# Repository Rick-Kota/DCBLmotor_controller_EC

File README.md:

# DCBLmotor_controller_EC
Electric Circuit data for DCBLmotor controller (in develop)

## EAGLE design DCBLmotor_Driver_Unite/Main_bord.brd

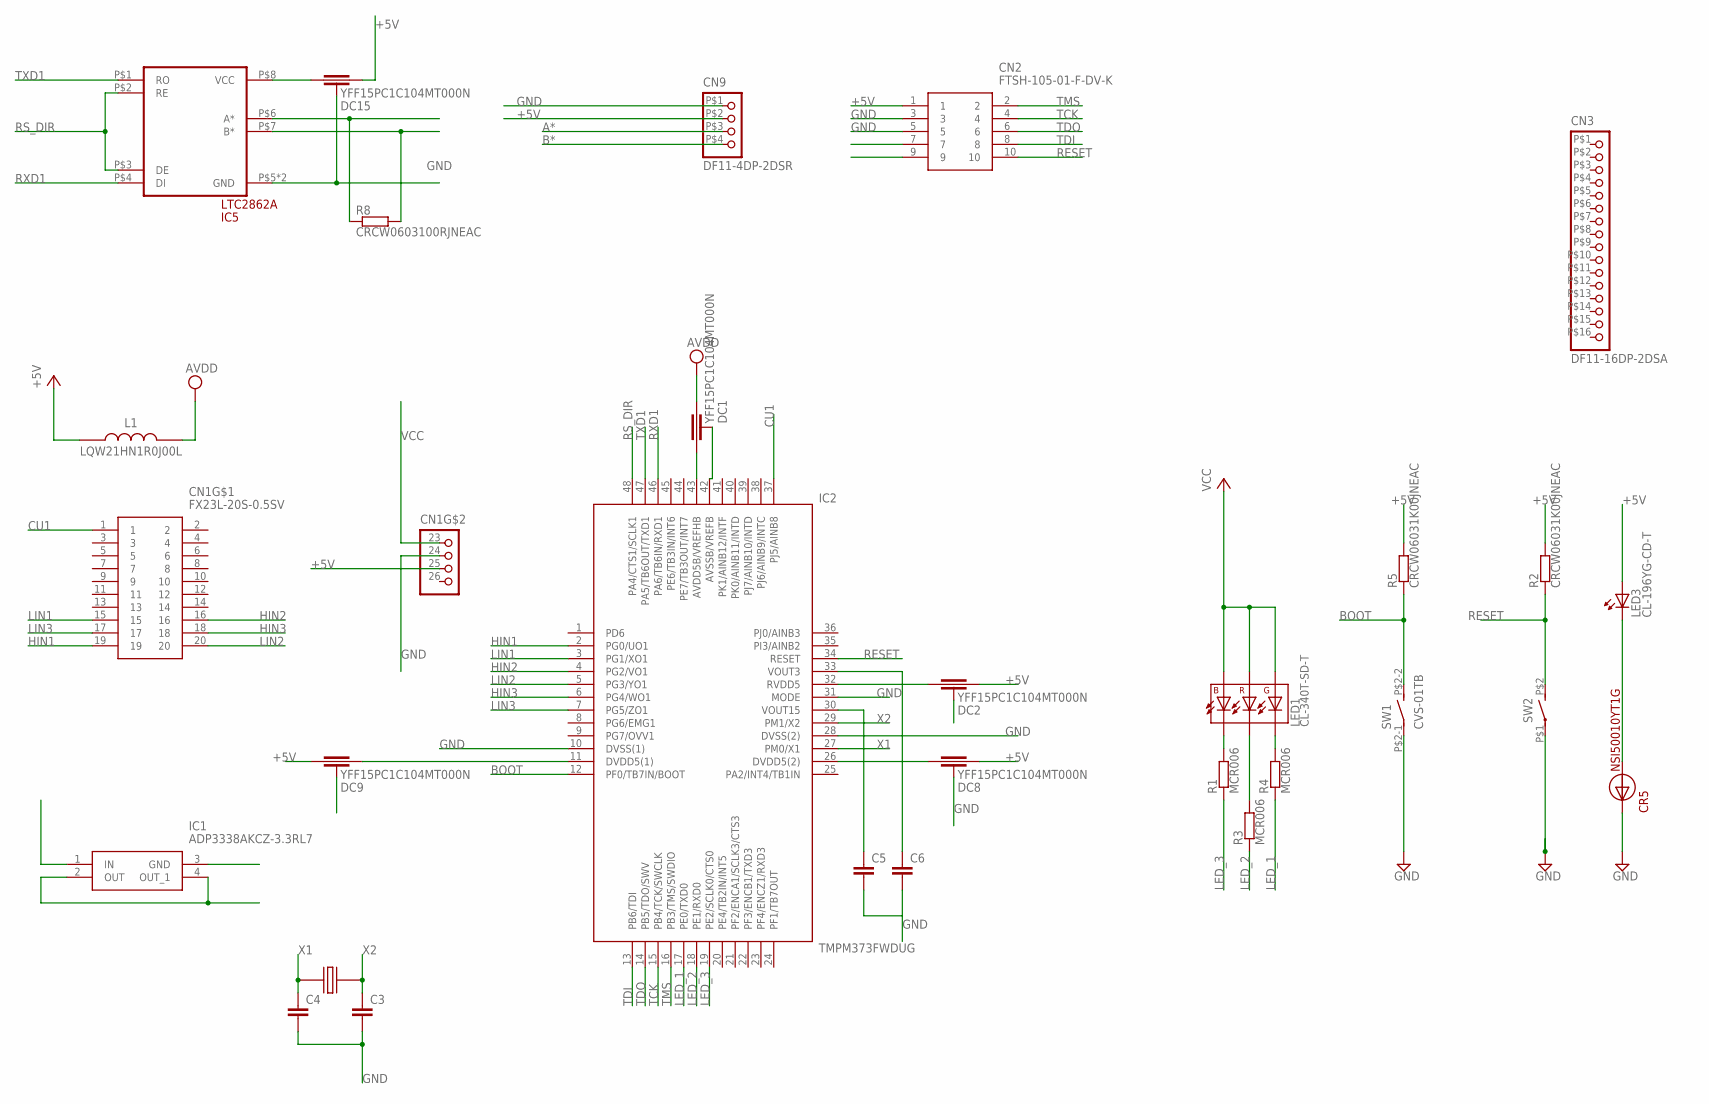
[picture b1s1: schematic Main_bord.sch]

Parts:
C3, C4: GRM0225C1E120JA03L; 0402
C5, C6: GRM035R60J475ME15D; 0603
CN1: FX23L-20S-0.5SV
CN2: FTSH-105-01-F-DV-K; SAMTEC_FTSH-105-01-L-DV
CN3: DF11-16DP-2DSA; DF11-16DP-2D
CN9: DF11-4DP-2DSR; DF11_4DP-2D
CR5: NSI50010YT1G; SOD-123
DC1, DC2, DC8, DC9, DC15: YFF15PC1C104MT000N; YFF15PC
IC1: ADP3338AKCZ-3.3RL7; SOT230P700X180-4N
IC2: TMPM373FWDUG; QFP50P900X900X160-48N
IC5: LTC2862A; DD_PACKGE_8
L1: LQW21HN1R0J00L; INDC2012X100N
LED1: CL-340T-SD-T; CL-340
LED3: CL-196YG-CD-T; CL-196
R1, R3, R4: MCR006
R2, R5: CRCW06031K00JNEAC; 0603
R8: CRCW0603100RJNEAC; 0603
SW1: CVS-01TB; CVS-01B
SW2: EVQ-PE104K; EVQ
XTAL1: ABM8AIG-10.000MHZ-12-2Z-T3; ABM8AIG

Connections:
+3.3V: IC1.2 (OUT), IC1.4 (OUT_1)
+5V: CN1.25 (3), CN2.1, CN9.P$2 (2), DC2.P$2, DC8.P$2, DC9.P$1, DC15.P$2, IC1.1 (IN), L1.1, LED1.P$1 (A_G), LED1.P$2 (R_A), LED1.P$3 (B_A), LED3.P$A (A), R2.P$1 (1), R5.P$1 (1)
A*: CN9.P$3 (3), IC5.P$6 (A*), R8.P$2 (2)
AVDD: DC1.P$2, L1.2
B*: CN9.P$4 (4), IC5.P$7 (B*), R8.P$1 (1)
BOOT: IC2.12 (PF0/TB7IN/BOOT), R5.P$2 (2), SW1.P$2-2 (S)
CU1: CN1.1, IC2.37 (PJ5/AINB8)
GND: C3.P$2 (2), C4.P$2 (2), C5.P$2 (2), C6.P$2 (2), CN1.24 (2), CN2.3, CN2.5, CN9.P$1 (1), CR5.P$C, DC1.P$3 (GND), DC1.P$4 (GND), DC2.P$3 (GND), DC2.P$4 (GND), DC8.P$3 (GND), DC8.P$4 (GND), DC9.P$3 (GND), DC9.P$4 (GND), DC15.P$3 (GND), DC15.P$4 (GND), IC1.3 (GND), IC2.10 (DVSS(1)), IC2.28 (DVSS(2)), IC2.31 (MODE), IC2.42 (AVSSB/VREFB), IC5.P$5 (GND), IC5.PAD (GND), SW1.P$2-1, SW2.P$1
HIN1: CN1.19, IC2.2 (PG0/UO1)
HIN2: CN1.16, IC2.4 (PG2/VO1)
HIN3: CN1.18, IC2.6 (PG4/WO1)
LED_1: IC2.17 (PE0/TXD0), R4.P$2 (2)
LED_2: IC2.18 (PE1/RXD0), R3.P$2 (2)
LED_3: IC2.19 (PE2/SCLK0/CTS0), R1.P$2 (2)
LIN1: CN1.15, IC2.3 (PG1/XO1)
LIN2: CN1.20, IC2.5 (PG3/YO1)
LIN3: CN1.17, IC2.7 (PG5/ZO1)
unnamed: DC2.P$1, IC2.32 (RVDD5)
unnamed: DC1.P$1, IC2.43 (AVDD5B/VREFHB)
unnamed: LED1.P$5 (R_C), R3.P$1 (1)
unnamed: LED1.P$4 (B_C), R1.P$1 (1)
unnamed: LED1.P$6 (G_C), R4.P$1 (1)
unnamed: C5.P$1 (1), IC2.30 (VOUT15)
unnamed: C6.P$1 (1), IC2.33 (VOUT3)
unnamed: DC8.P$1, IC2.26 (DVDD5(2))
unnamed: DC9.P$2, IC2.11 (DVDD5(1))
unnamed: CR5.P$A, LED3.P$C (C)
unnamed: DC15.P$1, IC5.P$8 (VCC)
RESET: CN2.10, IC2.34 (RESET), R2.P$2 (2), SW2.P$2 (S)
RS_DIR: IC2.48 (PA4/CTS1/SCLK1), IC5.P$2 (RE), IC5.P$3 (DE)
RXD1: IC2.46 (PA6/TB6IN/RXD1), IC5.P$4 (DI)
TCK: CN2.4, IC2.15 (PB4/TCK/SWCLK)
TDI: CN2.8, IC2.13 (PB6/TDI)
TDO: CN2.6, IC2.14 (PB5/TDO/SWV)
TMS: CN2.2, IC2.16 (PB3/TMS/SWDIO)
TXD1: IC2.47 (PA5/TB6OUT/TXD1), IC5.P$1 (RO)
VCC: CN1.23 (1)
X1: C4.P$1 (1), IC2.27 (PM0/X1), XTAL1.P$1
X2: C3.P$1 (1), IC2.29 (PM1/X2), XTAL1.P$3

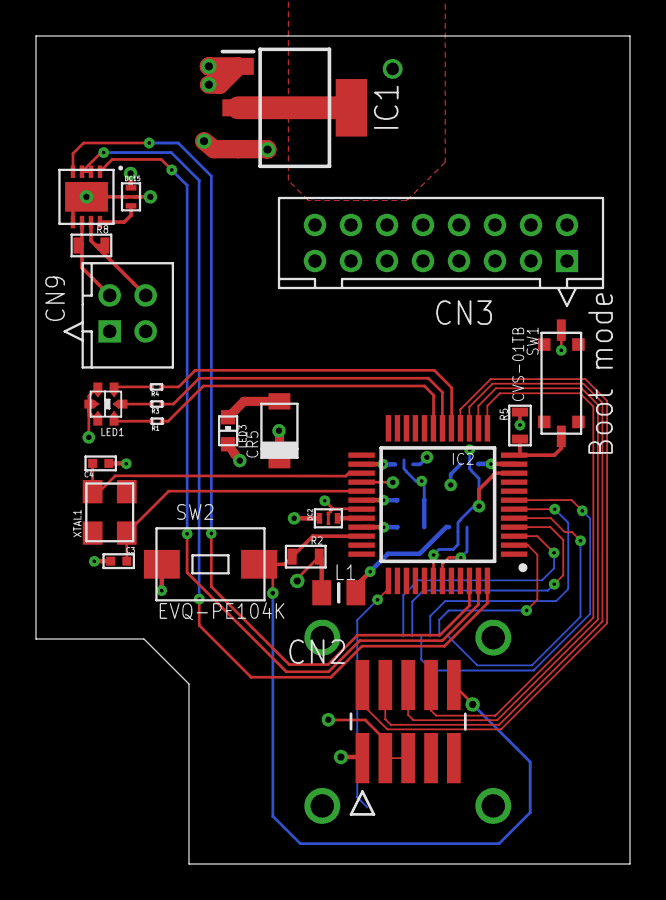
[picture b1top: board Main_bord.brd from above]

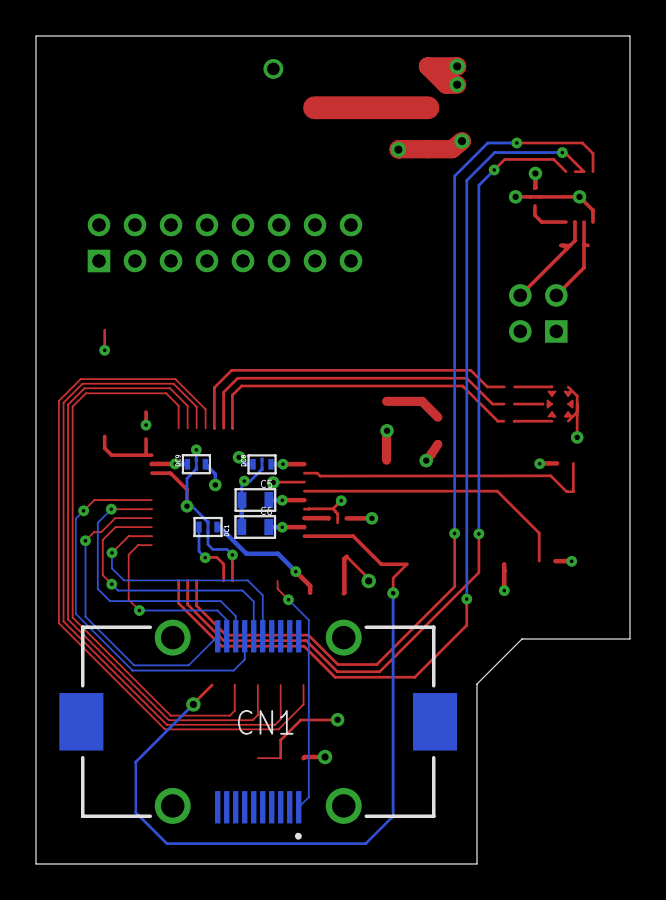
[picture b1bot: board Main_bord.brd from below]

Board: 4 copper layers, 33.0 x 46.0 mm, 29 parts (6 on the bottom side), 38 nets.

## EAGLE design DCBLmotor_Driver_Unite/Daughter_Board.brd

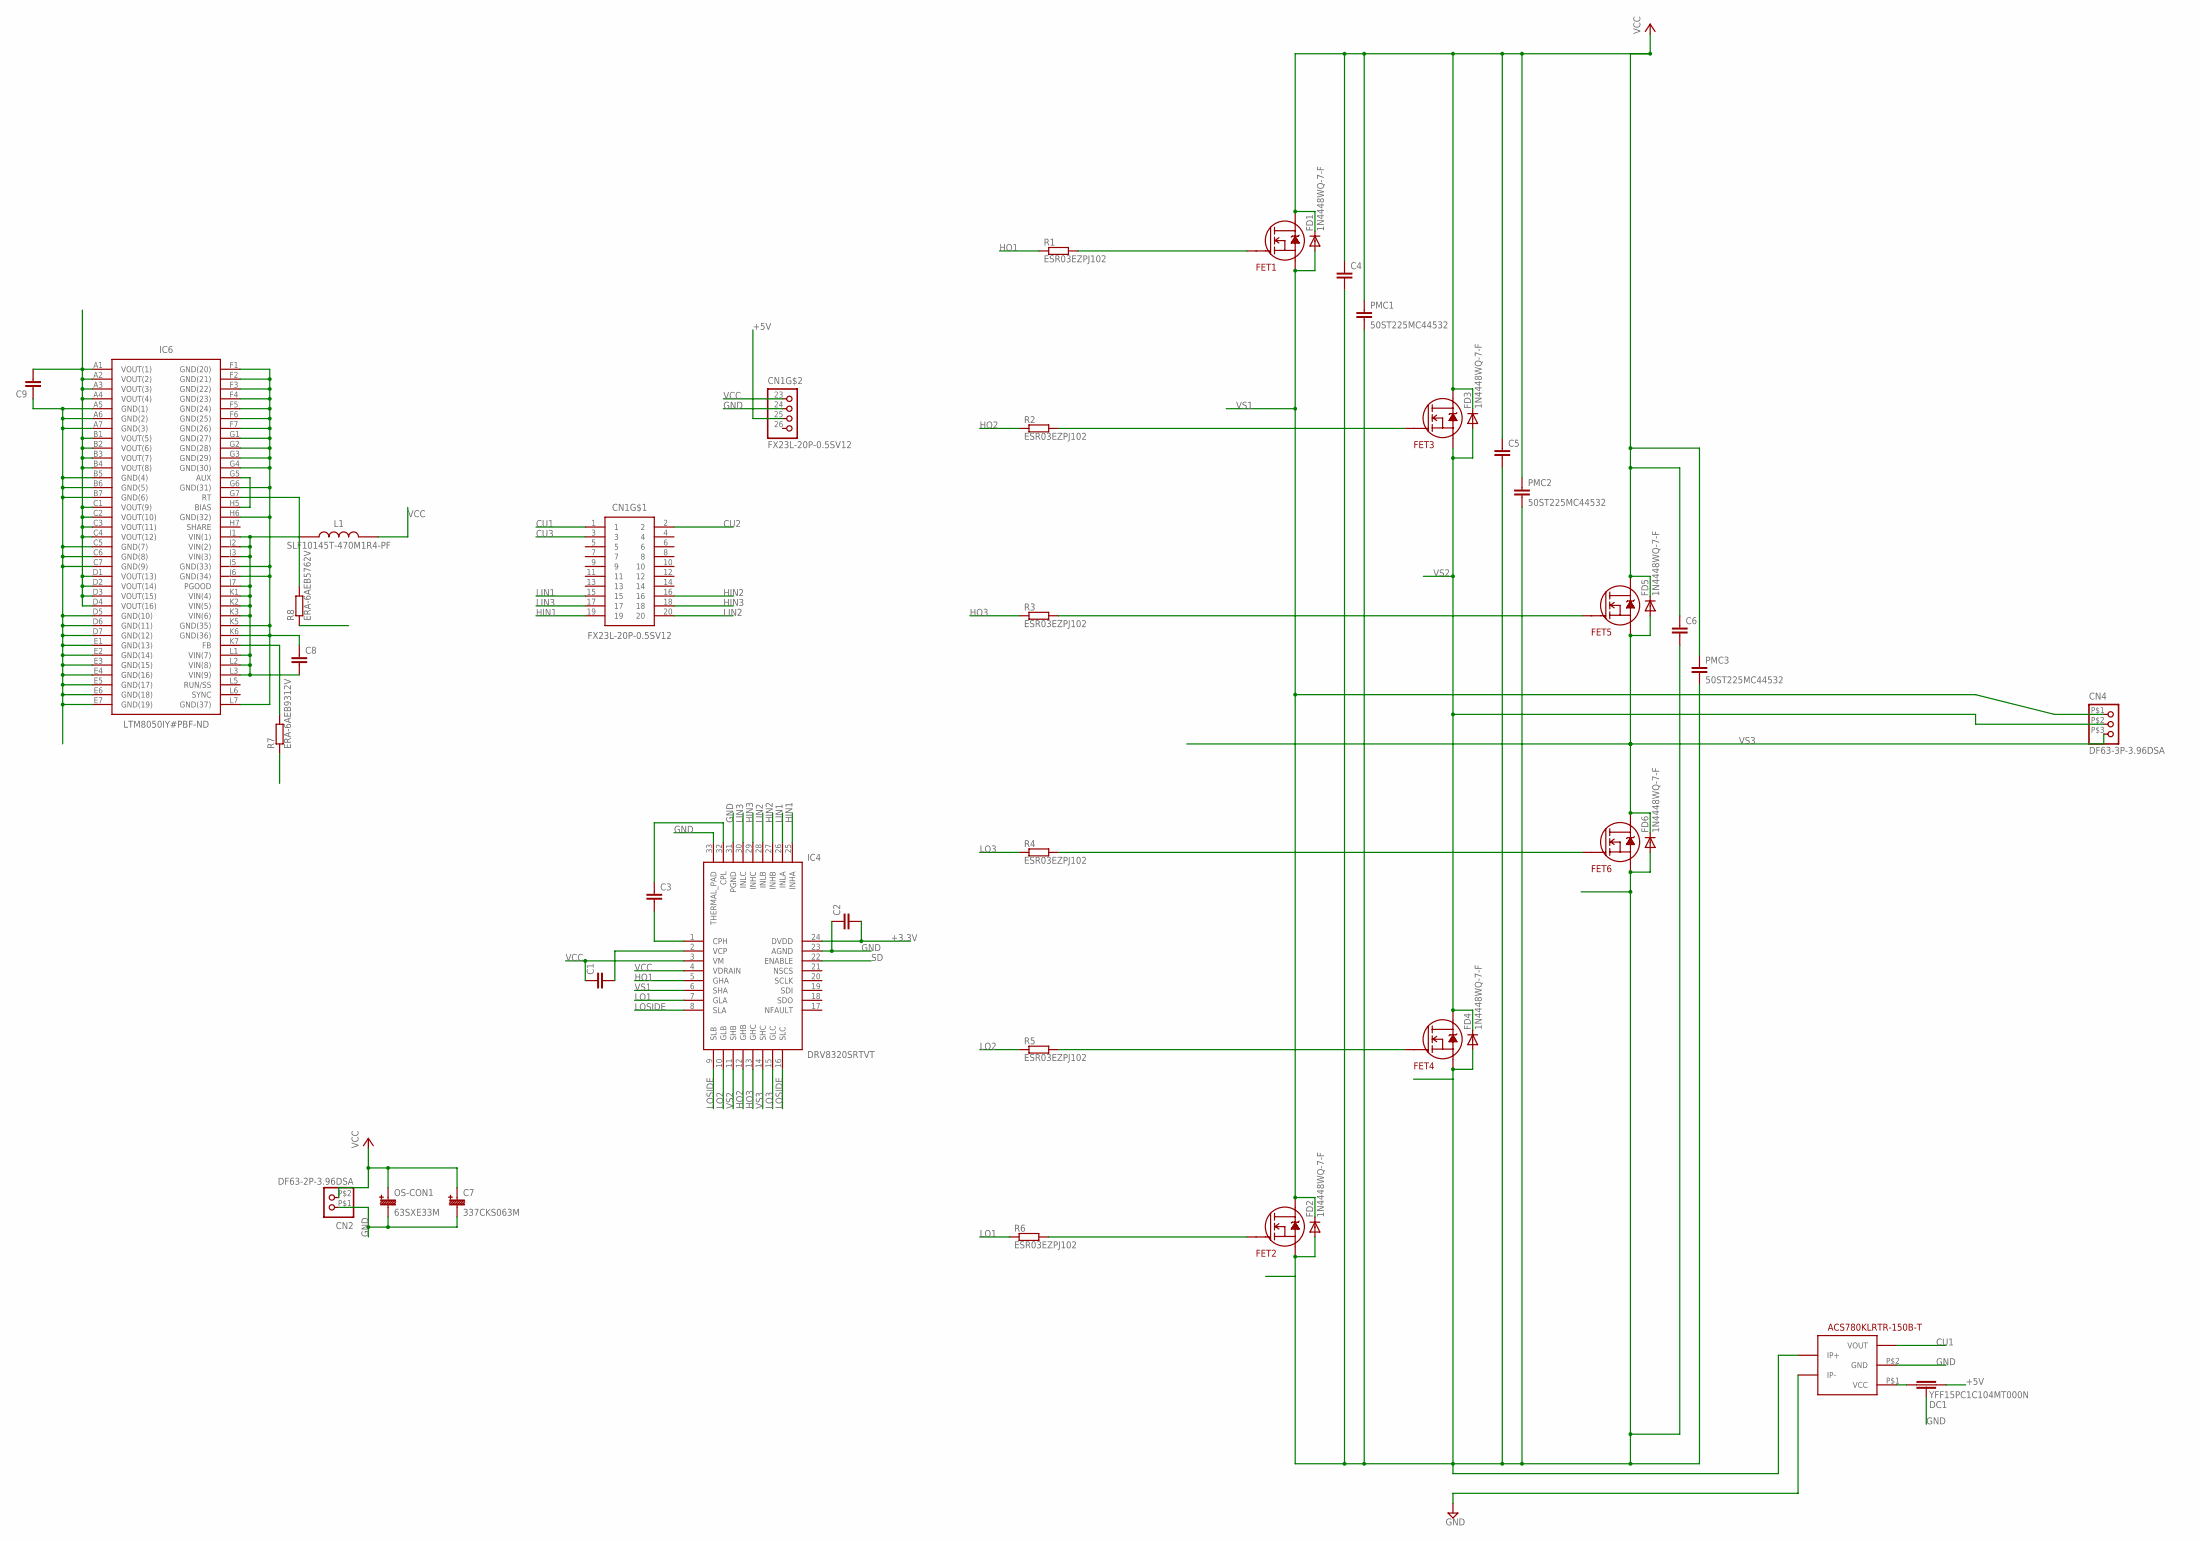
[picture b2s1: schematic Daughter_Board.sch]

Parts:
C1, C2, C4, C5, C6: CKG32KX7R1H105M335AJ; CGK32K
C3: CGA2B3X7R1H473K050BB; C0402
C7: 337CKS063M; 10
C8: CGA6M3X7S2A475M200AB; C1210
C9: GRM035R60J475ME15D; 0603
CN1: FX23L-20P-0.5SV12
CN2: DF63-2P-3.96DSA
CN4: DF63-3P-3.96DSA
DC1: YFF15PC1C104MT000N; YFF15PC
FD1, FD2, FD3, FD4, FD5, FD6: 1N4448WQ-7-F; SOD123
FET1, FET2, FET3, FET4, FET5, FET6: IRF7480MTRPBF; DIRECT_FET_ME
IC1: ACS780KLRTR-150B-T; 7-PIN_PSOP
IC4: DRV8320SRTVT; QFN50P500X500X80-33N
IC6: LTM8050IY#PBF-ND; BGA70C127P7X11_900X1500X512
L1: SLF10145T-470M1R4-PF; SLF10145
OS-CON1: 63SXE33M; E12
PMC1, PMC2, PMC3: 50ST225MC44532; 4532
R1, R2, R3, R4, R5, R6: ESR03EZPJ102; ESR03
R7: ERA-6AEB9312V; R0805
R8: ERA-6AEB5762V; R0805

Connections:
+3.3V: C2.P$2 (2), IC4.24 (DVDD)
+5V: C9.P$2 (2), CN1.25 (3), DC1.P$2, IC6.A1 (VOUT(1)), IC6.A2 (VOUT(2)), IC6.A3 (VOUT(3)), IC6.A4 (VOUT(4)), IC6.B1 (VOUT(5)), IC6.B2 (VOUT(6)), IC6.B3 (VOUT(7)), IC6.B4 (VOUT(8)), IC6.C1 (VOUT(9)), IC6.C2 (VOUT(10)), IC6.C3 (VOUT(11)), IC6.C4 (VOUT(12)), IC6.D1 (VOUT(13)), IC6.D2 (VOUT(14)), IC6.D3 (VOUT(15)), IC6.D4 (VOUT(16))
CU1: CN1.1, IC1.P$3 (VOUT)
CU2: CN1.2
CU3: CN1.3
GND: C2.P$1 (1), C7.P$- (2), C8.P$1 (1), C9.P$1 (1), CN1.24 (2), CN2.P$1 (1), DC1.P$3 (GND), DC1.P$4 (GND), IC1.P$2 (GND), IC1.P$6 (IP-), IC4.23 (AGND), IC4.31 (PGND), IC4.33 (THERMAL_PAD), IC6.A5 (GND(1)), IC6.A6 (GND(2)), IC6.A7 (GND(3)), IC6.B5 (GND(4)), IC6.B6 (GND(5)), IC6.B7 (GND(6)), IC6.C5 (GND(7)), IC6.C6 (GND(8)), IC6.C7 (GND(9)), IC6.D5 (GND(10)), IC6.D6 (GND(11)), IC6.D7 (GND(12)), IC6.E1 (GND(13)), IC6.E2 (GND(14)), IC6.E3 (GND(15)), IC6.E4 (GND(16)), IC6.E5 (GND(17)), IC6.E6 (GND(18)), IC6.E7 (GND(19)), IC6.F1 (GND(20)), IC6.F2 (GND(21)), IC6.F3 (GND(22)), IC6.F4 (GND(23)), IC6.F5 (GND(24)), IC6.F6 (GND(25)), IC6.F7 (GND(26)), IC6.G1 (GND(27)), IC6.G2 (GND(28)), IC6.G3 (GND(29)), IC6.G4 (GND(30)), IC6.G6 (GND(31)), IC6.H6 (GND(32)), IC6.J5 (GND(33)), IC6.J6 (GND(34)), IC6.K5 (GND(35)), IC6.K6 (GND(36)), IC6.L7 (GND(37)), OS-CON1.P$- (2), R7.2, R8.2
HIN1: CN1.19, IC4.25 (INHA)
HIN2: CN1.16, IC4.27 (INHB)
HIN3: CN1.18, IC4.29 (INHC)
HO1: IC4.5 (GHA), R1.P$2 (2)
HO2: IC4.12 (GHB), R2.P$2 (2)
HO3: IC4.13 (GHC), R3.P$2 (2)
IN_A: C8.P$2 (2), IC6.J1 (VIN(1)), IC6.J2 (VIN(2)), IC6.J3 (VIN(3)), IC6.J7 (PGOOD), IC6.K1 (VIN(4)), IC6.K2 (VIN(5)), IC6.K3 (VIN(6)), IC6.L1 (VIN(7)), IC6.L2 (VIN(8)), IC6.L3 (VIN(9)), L1.P$1 (1)
LIN1: CN1.15, IC4.26 (INLA)
LIN2: CN1.20, IC4.28 (INLB)
LIN3: CN1.17, IC4.30 (INLC)
LO1: IC4.7 (GLA), R6.P$2 (2)
LO2: IC4.10 (GLB), R5.P$2 (2)
LO3: IC4.15 (GLC), R4.P$2 (2)
LOSIDE: C4.P$2 (2), C5.P$2 (2), C6.P$2 (2), FD2.A, FD4.A, FD6.A, FET2.S1 (S), FET2.S2 (S), FET2.S3 (S), FET2.S4 (S), FET4.S1 (S), FET4.S2 (S), FET4.S3 (S), FET4.S4 (S), FET6.S1 (S), FET6.S2 (S), FET6.S3 (S), FET6.S4 (S), IC1.P$5 (IP+), IC4.8 (SLA), IC4.9 (SLB), IC4.16 (SLC), PMC1.P$2 (2), PMC2.P$2 (2), PMC3.P$2 (2)
unnamed: IC6.G5 (AUX), IC6.H5 (BIAS)
unnamed: FET4.G1 (G), FET4.G2 (G), R5.P$1 (1)
unnamed: IC6.K7 (FB), R7.1
unnamed: FET2.G1 (G), FET2.G2 (G), R6.P$1 (1)
unnamed: C1.P$2 (2), IC4.2 (VCP)
unnamed: IC6.G7 (RT), R8.1
unnamed: C3.P$2 (2), IC4.1 (CPH)
unnamed: C3.P$1 (1), IC4.32 (CPL)
unnamed: DC1.P$1, IC1.P$1 (VCC)
unnamed: FET6.G1 (G), FET6.G2 (G), R4.P$1 (1)
unnamed: FET5.G1 (G), FET5.G2 (G), R3.P$1 (1)
unnamed: FET3.G1 (G), FET3.G2 (G), R2.P$1 (1)
unnamed: FET1.G1 (G), FET1.G2 (G), R1.P$1 (1)
SD: IC4.22 (ENABLE)
VCC: C1.P$1 (1), C4.P$1 (1), C5.P$1 (1), C6.P$1 (1), C7.P$+ (+), CN1.23 (1), CN2.P$2 (2), FD1.K (C), FD3.K (C), FD5.K (C), FET1.P$1 (D), FET1.P$2 (D), FET1.P$3 (D), FET1.P$4 (D), FET3.P$1 (D), FET3.P$2 (D), FET3.P$3 (D), FET3.P$4 (D), FET5.P$1 (D), FET5.P$2 (D), FET5.P$3 (D), FET5.P$4 (D), IC4.3 (VM), IC4.4 (VDRAIN), L1.P$2 (2), OS-CON1.P$+ (+), PMC1.P$1 (1), PMC2.P$1 (1), PMC3.P$1 (1)
VS1: CN4.P$1 (1), FD1.A, FD2.K (C), FET1.S1 (S), FET1.S2 (S), FET1.S3 (S), FET1.S4 (S), FET2.P$1 (D), FET2.P$2 (D), FET2.P$3 (D), FET2.P$4 (D), IC4.6 (SHA)
VS2: CN4.P$2 (2), FD3.A, FD4.K (C), FET3.S1 (S), FET3.S2 (S), FET3.S3 (S), FET3.S4 (S), FET4.P$1 (D), FET4.P$2 (D), FET4.P$3 (D), FET4.P$4 (D), IC4.11 (SHB)
VS3: CN4.P$3 (3), FD5.A, FD6.K (C), FET5.S1 (S), FET5.S2 (S), FET5.S3 (S), FET5.S4 (S), FET6.P$1 (D), FET6.P$2 (D), FET6.P$3 (D), FET6.P$4 (D), IC4.14 (SHC)

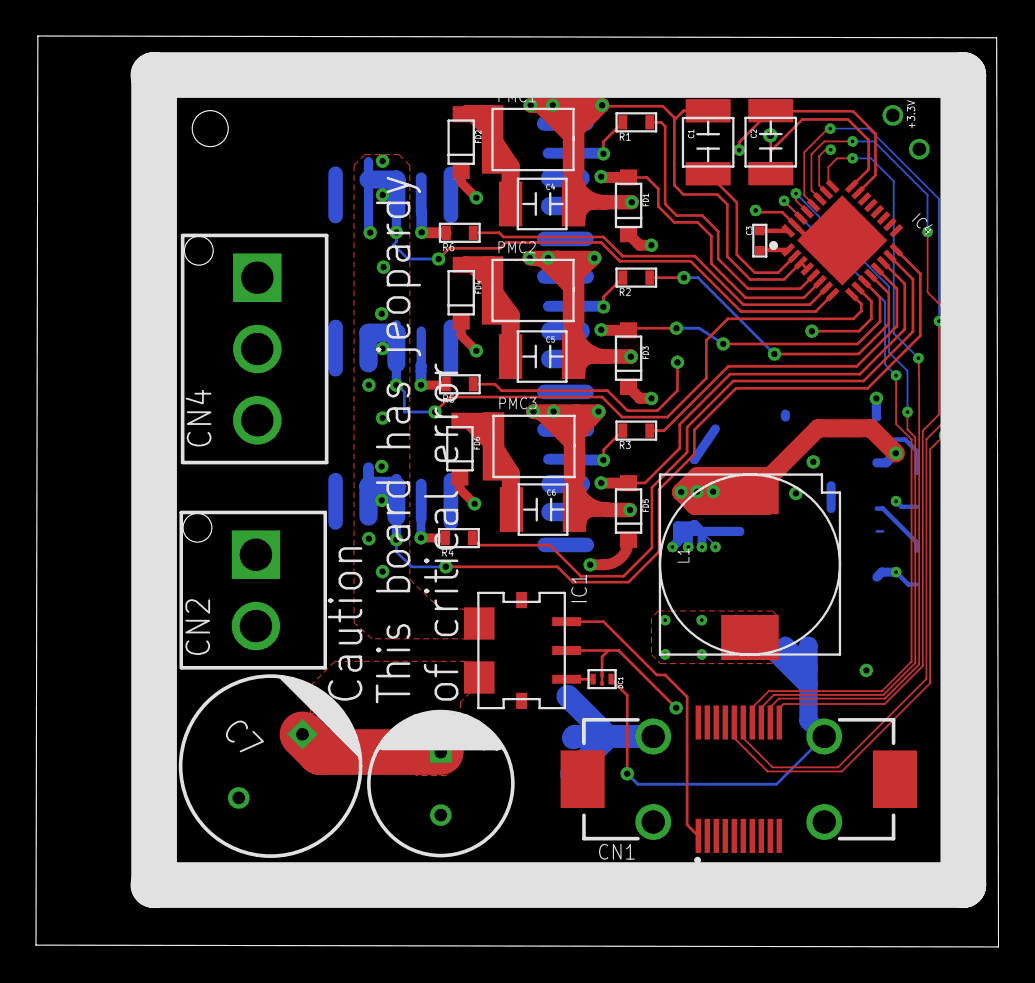
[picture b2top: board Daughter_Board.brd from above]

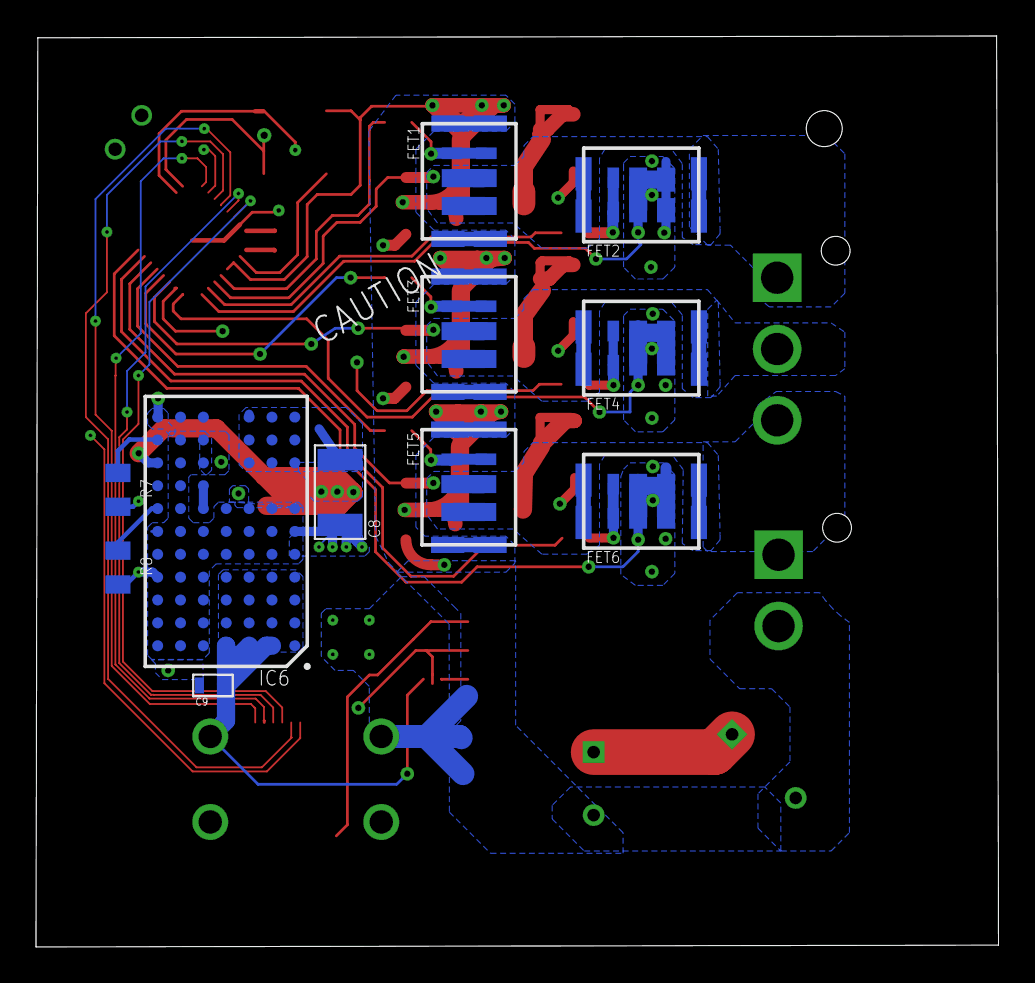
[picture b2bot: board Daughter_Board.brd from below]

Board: 4 copper layers, 53.5 x 50.6 mm, 41 parts (11 on the bottom side), 35 nets.

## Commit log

2017-10-10 Add files
2018-01-17 Add Libraries
2018-01-17 Build Daughter_bord
2018-01-17 build Main_board
2018-01-18 Mount Encoder parts
2018-01-18 Mount Endcoder
2018-01-19 Add new parts
    DF11 4pin holl
2018-01-19 add new parts
    add switch
2018-01-19 Add new parts
    6pin micro-fit
2018-01-19 Mount new parts
    mount
    holl conecter
    change
    reset switch
2018-01-19 Update .gitignore
    ignore to mac's system files
2018-01-21 fox of parts
    fixed silk position
2018-01-21 Add new parts
2018-01-21 Fix parts
    Fix pad position
2018-01-21 Fix Parts
2018-01-21 Version1 per finshed
    Per complete Version1
2018-01-21 Fix
    Add coment in silk
    rerote some line
    fix External form
    Add screw hole
2018-01-28 Assigned Parts No.
2018-01-29 Resister for Quartz crystalstal
2018-01-29 Add new parts
    LTM4623IY
2018-01-29 TEMP Reples parts
2018-01-30 Add LTM4623
2018-01-31 Repless to LTM4623
2018-02-01 Change Driver borard
    Change FETs and Gatedriver
2018-02-01 Build around FET
2018-02-16 Just before Delete MCU from daughter
2018-02-16 Attach DC-DC Converter
2018-02-16 TEMP Chenge MCU
2018-02-16 Change to 1 shant
2018-02-23 Main_borad is Almost_finshed
2018-03-02 Temp Commit
